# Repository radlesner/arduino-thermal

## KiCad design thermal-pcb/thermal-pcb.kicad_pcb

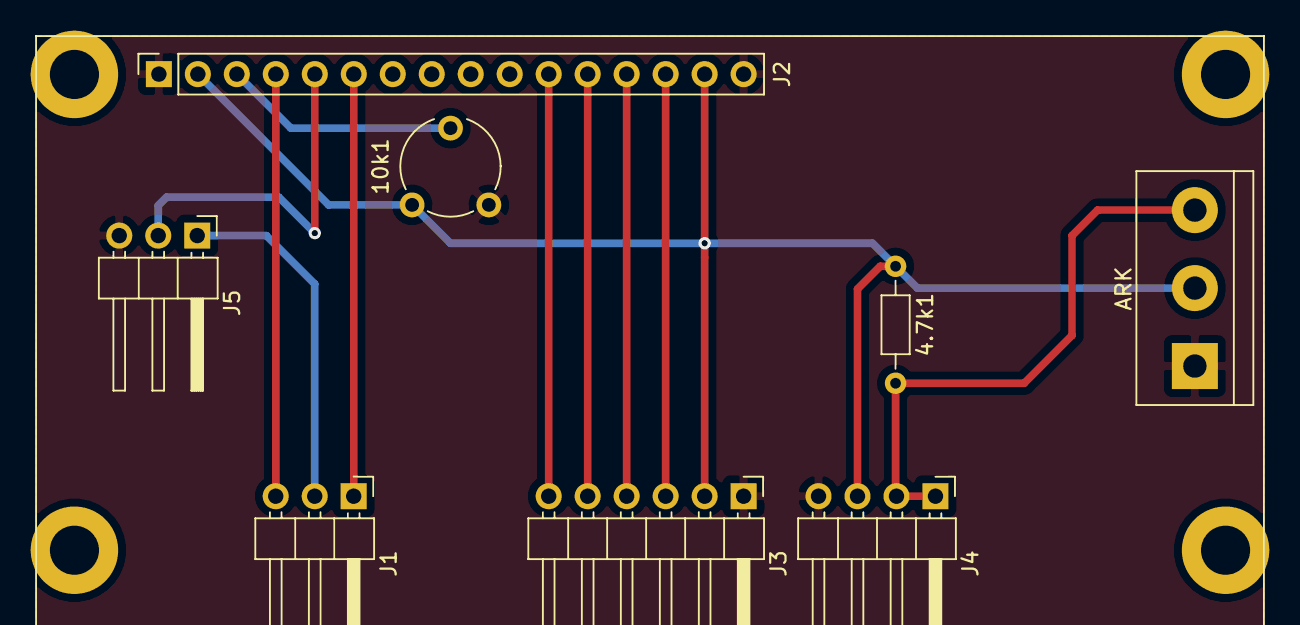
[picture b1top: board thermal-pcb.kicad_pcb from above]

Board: 2 copper layers, 8 parts (0 on the bottom side), 12 nets.

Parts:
4.7k1: R; R_Axial_DIN0204_L3.6mm_D1.6mm_P7.62mm_Horizontal
10k1: R_POT; Potentiometer_Piher_PT-6-V_Vertical
ARK: TerminalBlock_bornier-3_P5.08mm
J1: RS/E pins; PinHeader_1x03_P2.54mm_Horizontal
J2: Conn_01x16_Female; PinSocket_1x16_P2.54mm_Vertical
J3: Data and power pins; PinHeader_1x06_P2.54mm_Horizontal
J4: Temp sensor pins; PinHeader_1x04_P2.54mm_Horizontal
J5: Switch RW; PinHeader_1x03_P2.54mm_Horizontal

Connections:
+5V: 4.7k1.1, 10k1.3, ARK.2, J2.2, J2.15, J3.2, J4.3
GND: 10k1.1, ARK.1, J2.1, J2.16, J3.16, J4.4, J5.3
unnamed: 4.7k1.2, ARK.3, J4.1, J4.2
unnamed: 10k1.2, J2.3
unnamed: J1.3, J2.4
unnamed: J1.2, J5.1
unnamed: J1.1, J2.6
unnamed: J2.5, J5.2
unnamed: J2.11, J3.6
unnamed: J2.12, J3.5
unnamed: J2.13, J3.4
unnamed: J2.14, J3.3

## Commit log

2020-11-24 Create repository.
2020-11-25 Added more information in serial output.
2020-11-25 Organize files in repo.
2020-11-28 Refactor of code.
2020-11-29 Added ethernet shield implementation.
2020-11-29 Cleaning code.
2020-11-29 Improved serial output.
2020-11-29 Remove unnecessary comments. Add new ones as needed in the future.
2020-12-06 Added KiCad project PCB.
2020-12-07 Update PCB sheme.
2020-12-08 PCB track width has been updated.
2020-12-09 Updated PCB sheme.
2020-12-16 Update PCB scheme.
2020-12-22 Update PCB sheme (Stage I Complete)
2023-04-04 Update arduino-thermal.ino and cumulative update
2023-05-28 v0.2 - Added support for several DS18B20 sensors, the program displays the values in degrees Celsius on the LCD screen.
2023-06-01 Code fixes and comments
2023-06-01 Added basic button (in progres)
2023-06-01 Update arduino.json.
